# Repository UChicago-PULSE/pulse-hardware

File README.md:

# pulse-hardware
This is the central repository for documents related to PULSE-A hardware development. Each subteam has a folder containing documentation for their specific hardware. 

# Subteam Folders
Subteams are in charge of managing their respective folders in accordance with our teamwide git SOP. Please see the Git SOP document on Notion for more details.

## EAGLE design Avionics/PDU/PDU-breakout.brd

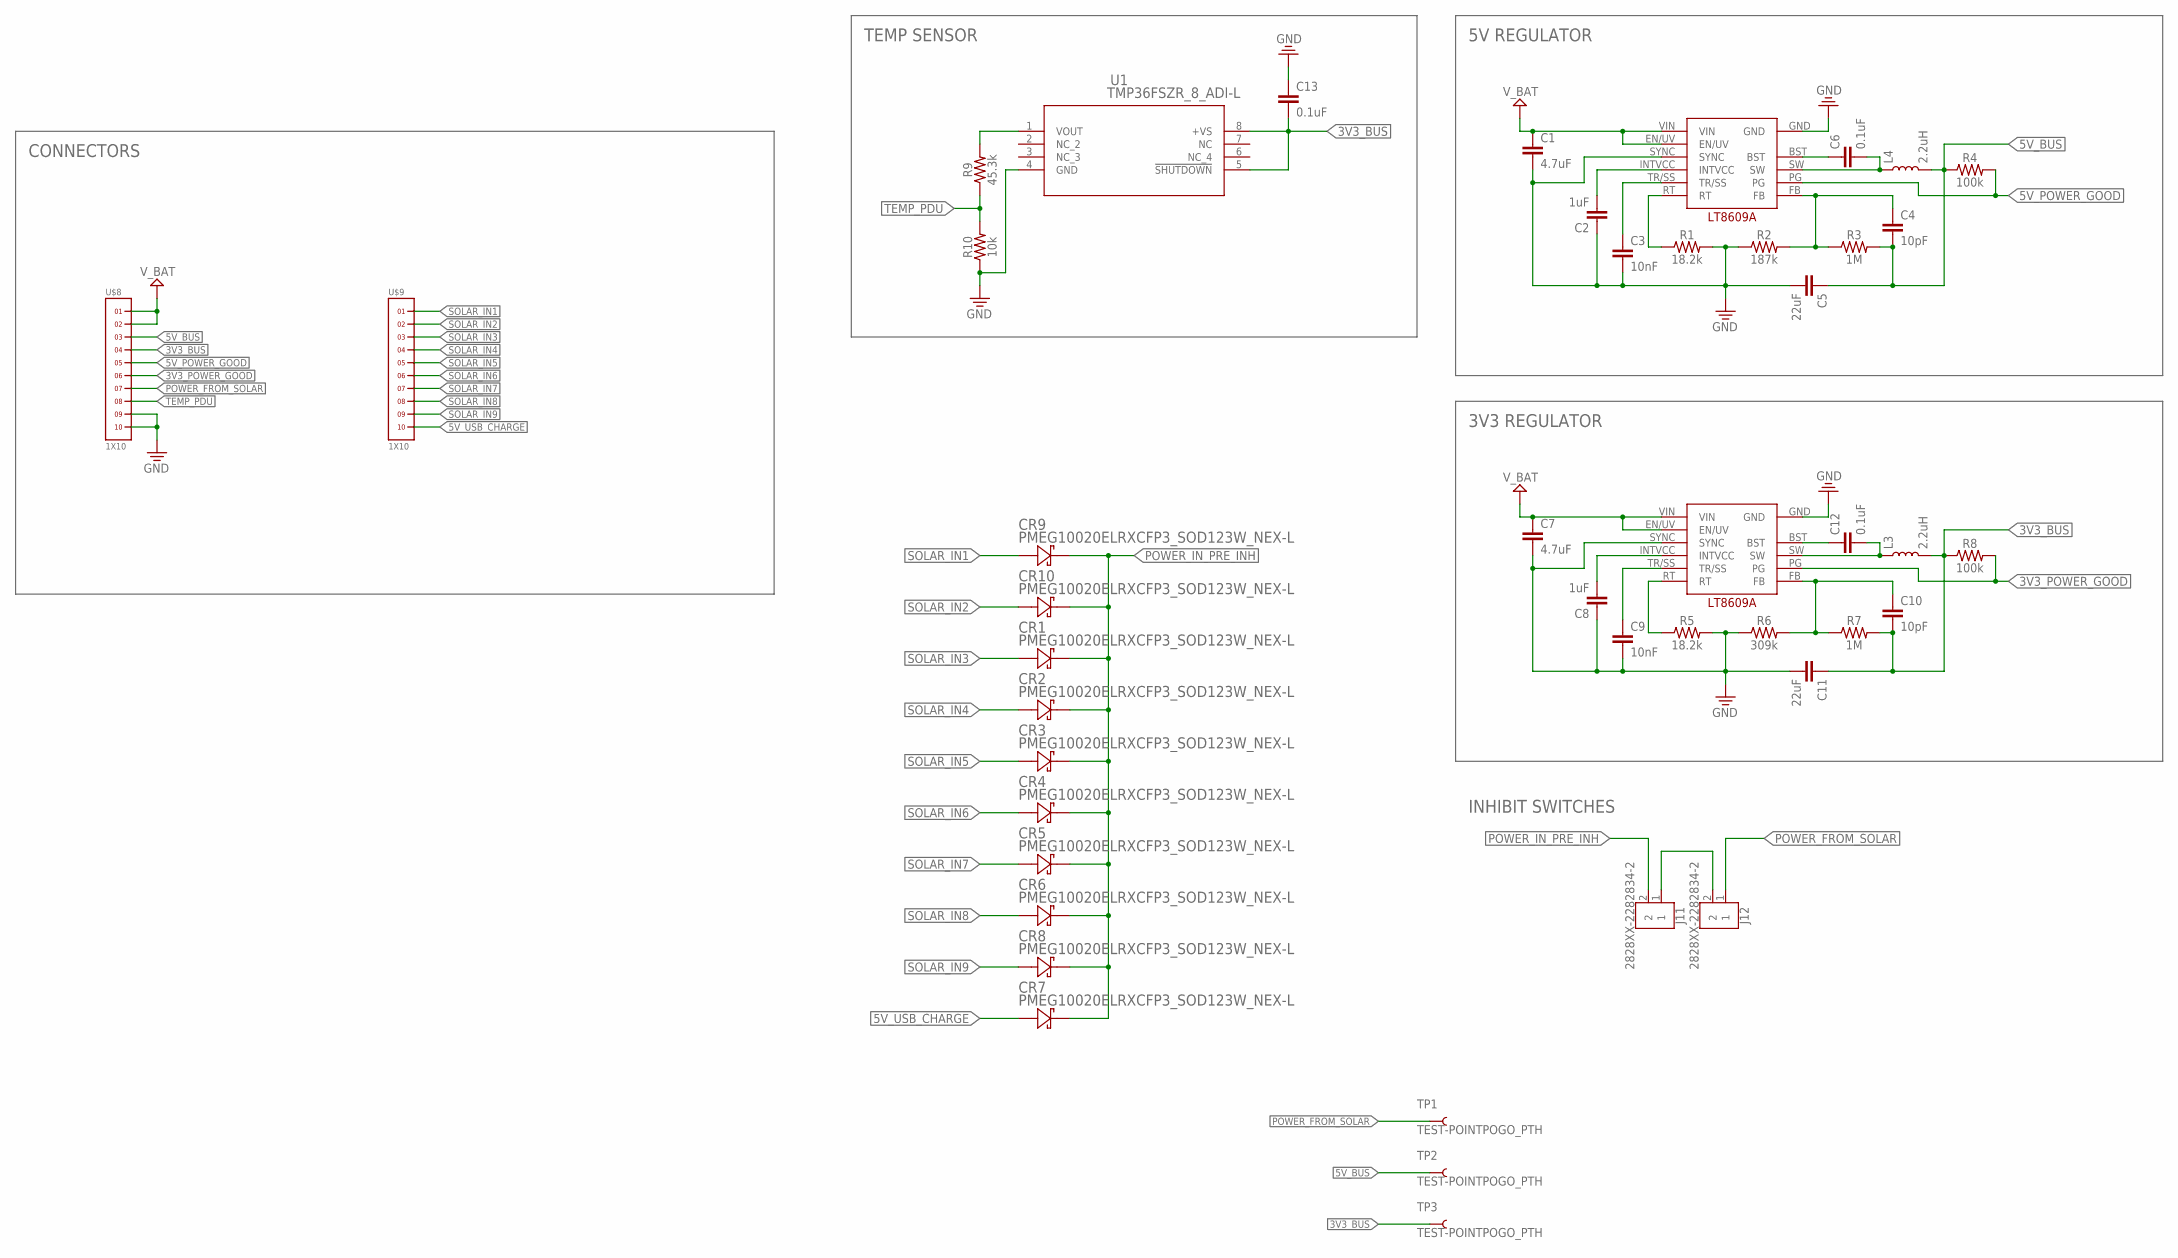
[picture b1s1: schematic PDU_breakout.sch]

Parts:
C1, C7: 4.7uF; 0805
C2, C8: 1uF; 0805
C3, C9: 10nF; 0805
C4, C10: 10pF; 0805
C5, C11: 22uF; 0805
C6, C12, C13: 0.1uF; 0805
CR1, CR2, CR3, CR4, CR5, CR6, CR7, CR8, CR9, CR10: PMEG10020ELRXCFP3_SOD123W_NEX-L; CFP3_SOD123W_NEX-L
J11, J12: 2828XX-2282834-2; TERMBLK_254-2N
L3, L4: 2.2uH; XFL4020
R1, R5: 18.2k; 0805
R2: 187k; 0805
R3, R7: 1M; 0805
R4, R8: 100k; 0805
R6: 309k; 0805
R9: 45.3k; 0805
R10: 10k; 0805
TP1, TP2, TP3: TEST-POINTPOGO_PTH; 1X01_NO_SILK
U1: TMP36FSZR_8_ADI-L; R_8_ADI-L
U$1, U$2: LT8609A-MSOP10; LT8609A-MSE10
U$8, U$9: 1X10

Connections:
3V3_BUS: C10.2, C11.1, C13.2, L3.P$2 (2), R7.2, R8.1, TP3.1, U1.5 (!SHUTDOWN), U1.8 (+VS), U$8.4
3V3_POWER_GOOD: R8.2, U$2.PG, U$8.6
5V_BUS: C4.2, C5.1, L4.P$2 (2), R3.2, R4.1, TP2.1, U$8.3
5V_POWER_GOOD: R4.2, U$1.PG, U$8.5
5V_USB_CHARGE: CR7.2 (12), U$9.10
GND: C1.2, C2.1, C3.2, C5.2, C7.2, C8.1, C9.2, C11.2, C13.1, R1.2, R2.1, R5.2, R6.1, R10.1, U1.4 (GND), U$1.GND, U$1.SYNC, U$2.GND, U$2.SYNC, U$8.9, U$8.10
unnamed: C6.1, U$1.BST
unnamed: C2.2, U$1.INTVCC
unnamed: C3.1, U$1.TR/SS
unnamed: R1.1, U$1.RT
unnamed: C8.2, U$2.INTVCC
unnamed: C4.1, R2.2, R3.1, U$1.FB
unnamed: C6.2, L4.P$1 (1), U$1.SW
unnamed: C9.1, U$2.TR/SS
unnamed: R5.1, U$2.RT
unnamed: C10.1, R6.2, R7.1, U$2.FB
unnamed: C12.1, U$2.BST
unnamed: R9.2, U1.1 (VOUT)
unnamed: C12.2, L3.P$1 (1), U$2.SW
unnamed: J11.1, J12.2
POWER_FROM_SOLAR: J12.1, TP1.1, U$8.7
POWER_IN_PRE_INH: CR1.1 (11), CR2.1 (11), CR3.1 (11), CR4.1 (11), CR5.1 (11), CR6.1 (11), CR7.1 (11), CR8.1 (11), CR9.1 (11), CR10.1 (11), J11.2
SOLAR_IN1: CR9.2 (12), U$9.1
SOLAR_IN2: CR10.2 (12), U$9.2
SOLAR_IN3: CR1.2 (12), U$9.3
SOLAR_IN4: CR2.2 (12), U$9.4
SOLAR_IN5: CR3.2 (12), U$9.5
SOLAR_IN6: CR4.2 (12), U$9.6
SOLAR_IN7: CR5.2 (12), U$9.7
SOLAR_IN8: CR6.2 (12), U$9.8
SOLAR_IN9: CR8.2 (12), U$9.9
TEMP_PDU: R9.1, R10.2, U$8.8
V_BAT: C1.1, C7.1, U$1.EN/UV, U$1.VIN, U$2.EN/UV, U$2.VIN, U$8.1, U$8.2

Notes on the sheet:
5V REGULATOR
3V3 REGULATOR
TEMP SENSOR
CONNECTORS
INHIBIT SWITCHES

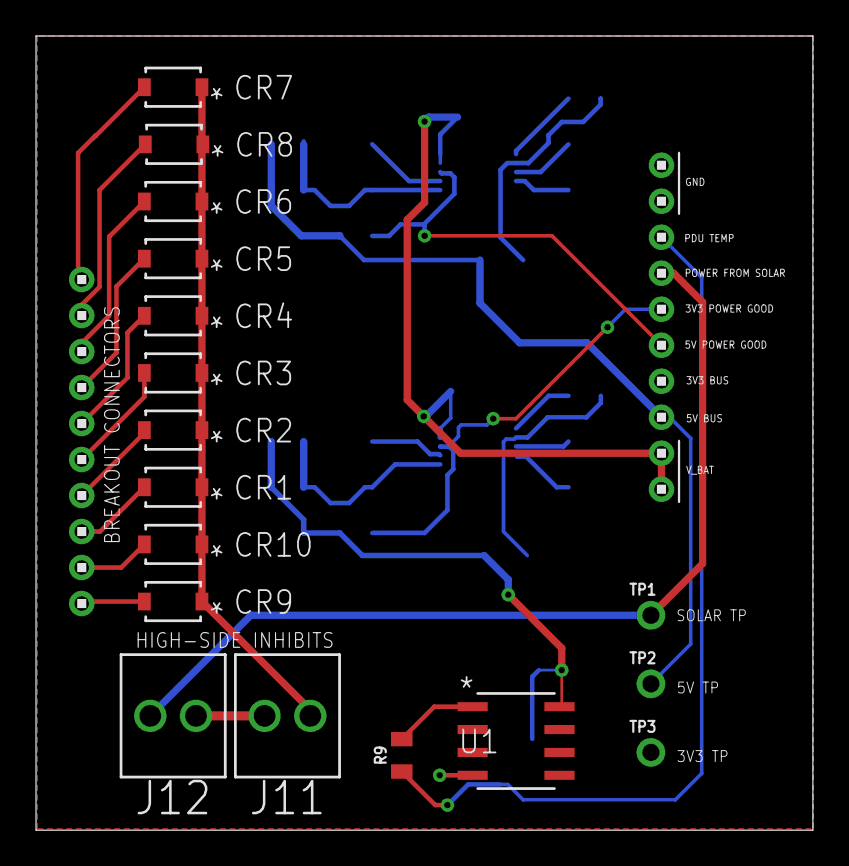
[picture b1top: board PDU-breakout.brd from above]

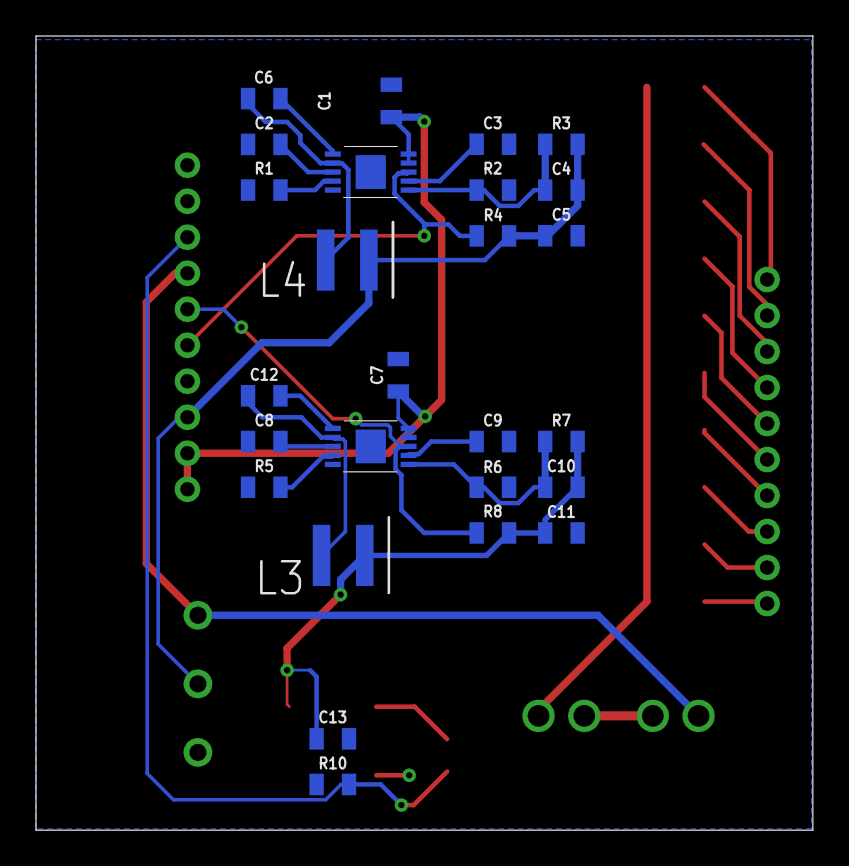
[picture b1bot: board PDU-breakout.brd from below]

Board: 2 copper layers, 43.2 x 44.1 mm, 45 parts (26 on the bottom side), 33 nets.

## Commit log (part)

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2023-09-07 Copied material over from HSFL artemis
    None of this is our work. Big thank you to HSFL.
2023-11-24 refactor and update readme
2024-06-04 initialize kicad files
2024-06-04 clear gitignore
2024-06-04 First try
2024-06-04 ignore .lck files
2024-06-04 init kicad files
2024-06-04 6.3.24 Ian Goldberg Made Changes to the README
2024-06-05 solar
2024-06-07 (6/7/24)(Ian Goldberg)Testing whether I am having issues pushing to GitHub
2024-06-07 (6/7/24)(Ian Goldberg) Added placeholder .gitkeep files to each subteam's directory such that github would track them. Made small edit to the README
2024-06-07 (6/7/24)(Ian Golberg) Replaced 5k Ohm resistor (number R44) with 10k Ohm resistor, thus R44 has been changed to 10k ohm. Capacitor number C12 was changed from 20 microfarad to 40 microfarad.
2024-06-07 (6/7/24)(Ian Goldberg) Removed example file used to write Github SOP on 6/7/24
2024-06-09 Ian Goldberg - Added a component library called powermanagementchip and made a component for the Texas instruments TPS65217CRSLR. Incorporated the chip into the design for the flight computer.
2024-06-09 Ian Goldberg - Added more components to the power regulation circuit. Havent yet added multiple sheets to the design. Refereincing the Beagleboard schematic PDF. Not sure whether KiCad automatically 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
2024-06-10 Ian Goldberg - Nearly completed the power regulator circuit for the flight computer. All parts of the circuit directly connected to the main chip (TPS65217CRSLR) have been designed. Hoping to finaliz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
2024-06-11 Demonstration of pushing
2024-06-11 Larry Li: created Quadcell files and created hamamatsu quadcell component. Need data on laser to claculate other components
2024-06-11 Made changes to the power regulator circuit in meeting on 6.10
2024-06-14 IanGoldberg; Added another sheet to the flight computer design containing (some) of the pins for the Texas Instruments SubArctic AM335x processor. Checked with others, all pins so far seem correct.
2024-06-15 Ian Goldberg - Made substantial additions to the main chip of the flight computer. Wrapping up progress for the night.
2024-06-15 Ian Goldberg - Made changes to the Flight Computer sheet
2024-06-15 Ian Goldberg - made final changes to the flight computer schematic
2024-06-17 Ian Goldberg - Made more progress on the SubArctic chip pin diagram; taking ages to finish. Had a few components I added to teh Subarctic library I made, but mught want to consolidate them into a glo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
2024-06-18 Ian Goldberg - Made more additions to the Subarctic chip
2024-06-18 Add files via upload
    Sephora Poteau,
    General Schematic for BOB. Created all components and provided separate sheets indicating interaction b/w said components. i.e. H1-H12.11.10 means that the indicated sheet shows how the H1-component 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
2024-06-18 Update and rename Avionics/H1-H12.11.10.kicad_sch to Avionics/BreakoutBoard/H1-H12.11.10.kicad_sch
    Moved File to BOB Folder
2024-06-18 Update and rename Avionics/H1-H14.13.kicad_sch to Avionics/BreakoutBoard/H1-H14.13.kicad_sch
    Moved File to BOB Folder
2024-06-18 Update and rename Avionics/H2-H12.11.10.kicad_sch to Avionics/BreakoutBoard/H2-H12.11.10.kicad_sch
    Moved File to BOB Folder
2024-06-18 Update and rename Avionics/H2-H14.13.kicad_sch to Avionics/BreakoutBoard/H2-H14.13.kicad_sch
    Moved File to BOB Folder
2024-06-18 Update README.txt to indicate what is in the BOB Folder
2024-06-18 Finished Quadcell Amp v1.0
2024-06-19 (Graydon SK) : PDU breakout initial commit
2024-06-19 Ian Goldberg - Finished the first shceet of the Subarctic Pin-outs. Still need to make some corrections on the voltage regulator circuit but that shouldn't take too long.
2024-06-20 Add files via upload
    Sephora Poteau, updates:
    - Adding where power is presumed to come from
    - Added where pins should be connected to GND on H3 and H4
    - Changed layout of H1 and H2 so that all symbols would be on one sheet
    - Adding footprints to all symbols
    - Created outline for board according to PC104 standards
2024-06-23 Ian Goldberg - Finished the second pin diagram for the SubArctic AM335x chip - only one more to go after this one.
2024-06-23 Ian Goldberg - Made some tricial changes to the second SubArctic pinout - should have corrected any errors in the pin labeling
2024-06-24 Ian Goldberg - Finished the pinout for the second sheet of the SubArctic chip and becan working on the connected circuitry
2024-06-28 Sephora Poteau: Added changes to schema and pcb
    Added 3V3 voltage indicator for power recieved by PCB and BOB has been appropriately traced and filled with copper
2024-06-28 Sephora Poteau: Created PC104 Folder and added README
2024-06-28 Create README.md in PC104LayoutFolder
2024-06-28 Sephora Poteau: Created Template for PC104
2024-06-28 Sephora Poteau: created PCB 104 Layout
2024-06-30 Ian Goldberg - Finished the pin-out for the third schematic of the SubArctic chip. All that remains is finishing up the rest of the circuit.
2024-07-05 Ian Goldberg - Added the 4th sheet to the flight computer schematic{
2024-07-12 Ian Goldberg - Making updates to the design for the flight computer
2024-07-16 Ian Goldberg - Finished the 7th sheet of the Flight Computer schematic.
2024-07-23 Ian Goldberg - Added a 7th sheet to the flight computer schematic
2024-07-23 Sephora Poteau: uploaded finished schematic and battery board
2024-07-23 Sephora Poteau: Cut the edges of the board and aligned it to PC104 layout
2024-07-23 Sephora Poteau: Added temperature sensor and terminal block connectors to Battery Board
2024-08-03 Ian Goldberg - Created a motherboard for the BeagleBone to alow ot to be mounted in the PC104 stack
2024-08-07 Ian Goldberg - finished the pc104 pinout for the beaglebone motherboard
2024-08-10 feat: PDU updates
2024-08-13 Finally (tentatively) finished the schematic for the PCI104 header pin bank. Yay.
2024-08-17 Ian Goldberg - Almost finishes with the PC104 Layout,
2024-08-20 feat: pdu updates (inc. pci104)
2024-08-22 Ian Goldberg - Added the pins necessary for Graydon's burn wire circuit
2024-08-22 Ian Goldberg - Finished the footprint for the BeagleBonePCI104 Motherboard
2024-08-24 Ian Goldberg - Finally finished the breakout board for the BeagleBone Black. Hoping to order the connectors soon and then asemble it.
2024-08-24 Ian Goldberg - pushed a correction to the BeagleBone Motherboard
2024-08-25 Ian Goldberg - Finished Version 2 of the flight computer, added a temperature sensor to the board.
2024-08-26 Ian Goldberg - Finished the second version of the flight computer board
2024-08-29 Ian Goldberg - Corrected DRC errors on battery board and generated gerber files to order
2024-09-13 Ian Goldberg - Made changes to the third revision of the flight computer board, trying to figure out a way to power it throught ht header connector while still extracting data (through ethernet).
2024-09-13 missing some stuff
2024-09-15 need to add net classes
2024-09-15 Ian Golberg - Tentatively Finalized v3 of the flight computer board.
2024-09-15 schematic almost done:
2024-09-16 Ian Goldberg - Finished Rev. 3 of the Flight Computer PCB.
2024-09-25 run checks
2024-09-29 all but Q1
2024-10-06 PDU 1.0.0
2024-10-06 Ian Goldberg - Pushing preliminary versions of version 4
2024-10-13 Adding new Batt_BoardV1
2024-10-14 quadcell 1014
2024-10-20 yippie
2024-10-20 need to fic tracks
2024-10-21 Quadcell PD 2.0 finished
2024-10-24 back to the schematic drawing board
2024-10-24 added USA flags to pulse footprint library
2024-10-27 schematic done
2024-11-10 just need traces
2024-11-14 added UCSP pngs
2024-11-29 feat: PDU 2.0.0
2024-12-03 12/3/2024, Sephora Poteau: changed PC104 layout to include copper layer and edge cuts, and changed placement of components on Batt_Boardv2
2024-12-04 meeting
2024-12-04 feat: batt & PDU progress
2024-12-05 12/5/2024, Sephora Poteau: Changed Layout of BattBoardPCB to lay traces
2024-12-05 12/5/2024, Sephora Poteau: Capasitors and Resistors have been traced, need to trace rest of board
2024-12-06 12/5/2024, Sephora Poteau: Finished the traces for all parts of the battery board.
2024-12-06 12/5/2024, Sephora Poteau: Finished adding traces, copper filled both front and back layers
2024-12-06 12/5/2024, Sephora Poteau: Fixed form of traces
2024-12-07 12/6/2024, Sephora Poteau: fixed traces, made all stack-through connectors be connected to ground
2024-12-07 12/6/2024, Sephora Poteau: Added GNDREF to appropriate pads
2024-12-07 12/6/2024, Sephora Poteau: Added GNDREF to appropriate pads and fixed copper fill on front plate
2024-12-18 12/17/2024, Sephora Poteau: Made power traces 0.7mm and fixed zones on front and back plate
2024-12-18 12/17/2024, Sephora Poteau: Replaced power traces with filled zones
2024-12-18 12/18/2024, Sephora Poteau: Added power planes to Batt_Boardv2 and increased clearance by 1mm
2024-12-18 Rev2 Quadcell Amp
2025-01-06 PDU 3.0.0
2025-01-23 flipped op amp signs :/
2025-02-20 feat: Batt Board v2, PDU v3 in progress; refactor: various cleanups
2025-02-20 fix: remove .DS_Store
2025-02-22 removed broken file
2025-03-09 added voltage divider and adjusted routing of quadcell
2025-03-09 small tweak from previous push
2025-03-09 a few more small tweaks to quadcell
2025-03-11 added voltage divider to quadcell
2025-03-15 added voltage regulator
2025-03-23 aesthetic changes + added zumi's name
2025-03-23 changed gnd plane
2025-03-28 added intermediary connectors and voltage caps after stage 1
2025-03-28 batt_brd: balance ic ref impl, renamed some stuff
    * Added BQ292xx balance IC reference implementation (see datasheet)
    * Changed GNDREF symbols to correct ones
    * Renamed cell holders to make more sense
2025-04-08 batt_brd: reorg sch, add sub sch for heater ctrl
    * Reorganized schematic
    * removed temp sensor
    * add sub schematic for heater control
2025-04-08 batt_brd: remove fp-info-cache and gitignore it
2025-04-08 batt_brd: add i2c labels on pc104
2025-04-09 misc: try to fix gitignore?
2025-04-09 batt_brd: add temp sensors and adc ic
    * Add 4x LM135 temperature sensors
    * Add TLA2024 ADC to read sensors
2025-04-09 batt_brd: add passive values for temp sensing
2025-04-13 batt_brd: move external symbols into proj tree
2025-04-13 batt_brd: make R5460 lib in proj dir
2025-05-18 (5/18/25)(Ned Sigler) removed crossing wires
2025-06-24 batt_brd: add TPS7A2650 symbol
2025-06-24 batt_brd: switch to TMP/LM35s
2025-06-24 batt_brd: discrete heater control has own 5v ldo
2025-07-04 batt_brd: prettify
2025-07-04 batt_brd: add decoupling caps & fix comparator output
2025-07-04 batt_brd: more labels
2025-07-07 batt_brd: clean up and add most footprints
2025-07-07 batt_brd: Update battery footprints
2025-07-28 "Finish" routing
    DRC failing; will fix soon
2025-07-28 resolve some drc things; add custom jlc drc rules
2025-07-29 feat: move subsystem docs to pulse-hardware
2025-07-29 refactor: reorganize repository
    have fun merging or rebasing :)
2025-07-29 refactor: move shit around
2025-08-01 clear up drcs; make pour clearance larger; optimize a bit
2025-08-01 reorganizw
2025-08-01 hidafasf
2025-08-01 fixes
2025-08-01 fdfsdfs
2025-08-05 reroute
2025-08-05 started quadcell documentation
2025-08-08 OwenLaw-1
2025-08-08 (7th August)(Owen Law) Added documntation of Radio-GPS board
2025-08-08 (7th August)/(le 19 Thermidor) (Owen Law) Added to gnc/overview.adoc
2025-08-08 feat: quadcell documentation and some index/overview documents
2025-08-09 batt_brd: documentation
2025-08-10 feat: moving GPS pcb, adding images to quadcell, edits to index and subsystems overview
2025-08-10 fix: quadcell page edits and added links to home page
2025-08-10 fix: radio edits
2025-08-10 (le 21 Thermidor/ 10 August) (Added GPS and Radio Purpose, Owen Law)
2025-08-10 nav.adoc adjustments
2025-08-11 Create CAD models
2025-08-12 batt_brd: reroute to optimize cu pour currentpaths
2025-08-19 batt_brd: gitignore gerbers
2025-08-27 Added Space Maniac final board design 27th Aug, Owen Law
2025-09-16 Revert "batt_brd: move to new directory (not sure why it wasn't there to begin with...)"
    This reverts commit cc26fb92c5d21fd22915d8e0022195de5c7e5fed.
2025-09-16 batt_brd: export bom
2025-09-29 feat added new op amps and fied voltage divider problem on qc board
2025-10-09 new quadcell rev
2025-10-09 fix: connected stage2
2025-10-23 qc amp changes

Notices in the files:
parts and their libraries:
SparkFun-Capacitors: Licensing: Creative Commons ShareAlike 4.0 International - https://creativecommons.org/licenses/by-sa/4.0
COPYRIGHT: Copyright (C) 2018 Accelerated Designs. All rights reserved
COPYRIGHT: Copyright (C) 2021 Ultra Librarian. All rights reserved.
